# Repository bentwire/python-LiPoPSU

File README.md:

# python-LiPoPSU
Python drivers and sundry for my LiPo PSU design in eagle

Boards can be ordered from OSH Park

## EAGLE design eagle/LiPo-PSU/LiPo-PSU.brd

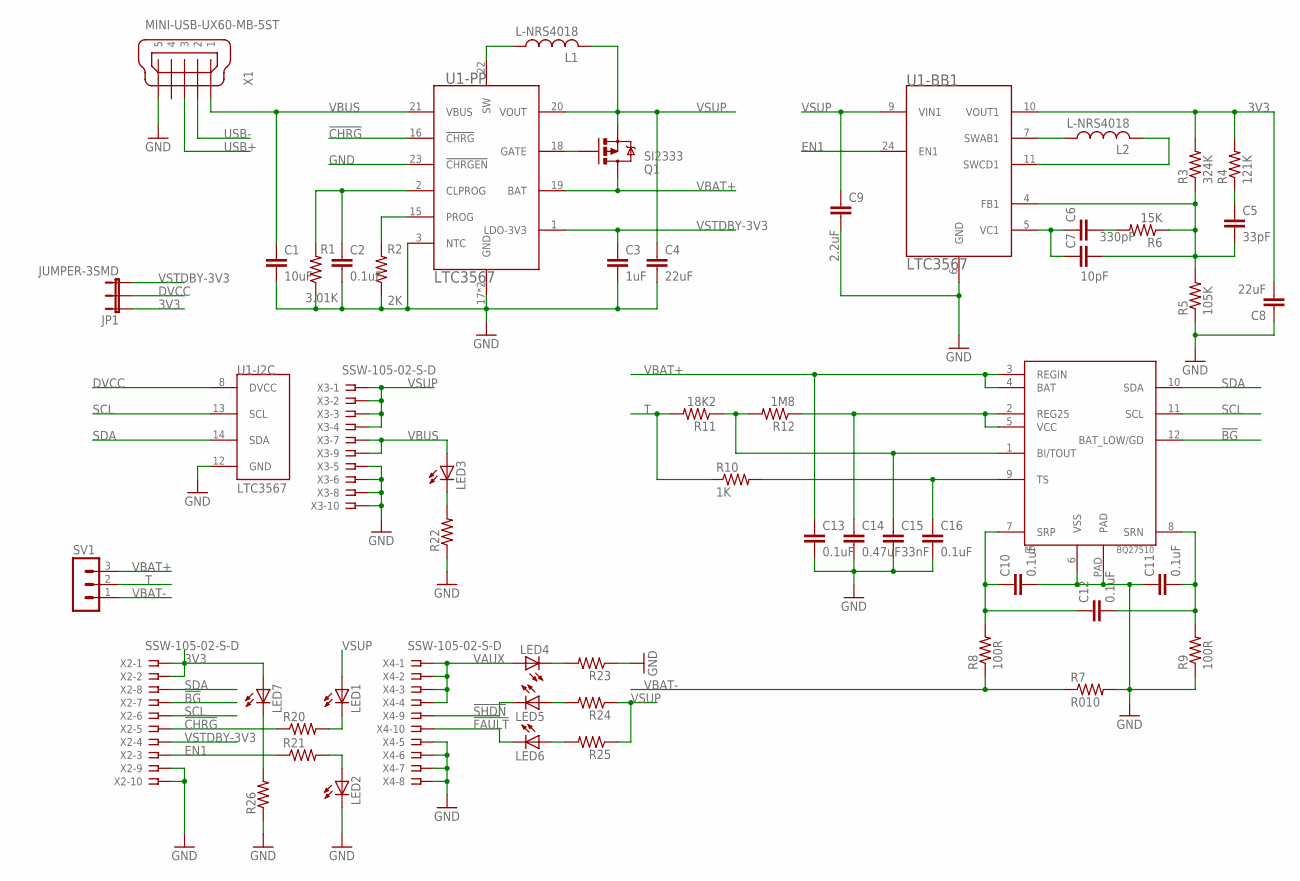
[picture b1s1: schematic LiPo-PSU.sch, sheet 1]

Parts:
C1: 10uF; 0805
C2: 0.1uF; 0402-CAP
C3: 1uF; 0402-CAP
C4, C8: 22uF; 0805
C5: 33pF; 0402-CAP
C6: 330pF; 0402-CAP
C7: 10pF; 0402-CAP
C9: 2.2uF; 0402-CAP
C10, C11, C12, C13, C16: 0.1uF; C0402
C14: 0.47uF; C0402
C15: 33nF; C0402
JP1: JUMPER-3SMD; SJ_3
L1, L2: L-NRS4018; NR(S)401X
LED1, LED2, LED3, LED4, LED5, LED6, LED7: LEDCHIP-LED0603; CHIP-LED0603
Q1: SI2333; SOT23-3
R1: 3.01K; 0402-RES
R2: 2K; 0402-RES
R3: 324K; 0402-RES
R4: 121K; 0402-RES
R5: 105K; 0402-RES
R6: 15K; 0402-RES
R7: R010; R2512
R8, R9: 100R; R0402
R10: 1K; R0402
R11: 18K2; R0402
R12: 1M8; R0402
R20, R21, R22, R23, R24, R25, R26: R-US_R0402; R0402
SV1: MA03-1
U1: LTC3567; QFN24-4X4(UF)
U3: BQ27510; DRZ(S-PDSO-N12)
X1: MINI-USB-UX60-MB-5ST; UX60-MB-5ST
X2, X3, X4: SSW-105-02-S-D

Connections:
3V3: C8.2, JP1.1, LED7.A, R3.2, R4.2, U1.10 (VOUT1), X2.1, X2.2; also elsewhere on the board
!BG: U3.12 (BAT_LOW/GD), X2.7
!CHRG!: R20.1, U1.16 (!CHRG!), X2.5
!FAULT: LED6.C, X4.10; also elsewhere on the board
!SHDN: LED5.C, X4.9; also elsewhere on the board
DVCC: JP1.2, U1.8 (DVCC)
EN1: R21.1, U1.24 (EN1), X2.3
GND: C1.2, C2.2, C3.2, C4.2, C8.1, C9.2, C10.2, C11.1, C13.2, C14.2, C15.2, C16.2, LED2.C, R1.1, R2.1, R5.1, R7.2, R9.1, R22.1, R23.1, R26.1, U1.3 (NTC), U1.6 (GND), U1.12 (GND), U1.17 (GND), U1.23 (!CHRGEN!), U1.PAD (GND), U3.6 (VSS), U3.PAD, X1.5, X2.9, X2.10, X3.5, X3.6, X3.8, X3.10, X4.5, X4.6, X4.7, X4.8; also elsewhere on the board
unnamed: L1.1, U1.22 (SW)
unnamed: C5.2, C7.2, R3.1, R5.2, R6.1, U1.4 (FB1)
unnamed: Q1.1 (G), U1.18 (GATE)
unnamed: L2.1, U1.7 (SWAB1)
unnamed: L2.2, U1.11 (SWCD1)
unnamed: C5.1, R4.1
unnamed: C15.1, R11.1, R12.2, U3.1 (BI/TOUT)
unnamed: C6.2, R6.2
unnamed: C6.1, C7.1, U1.5 (VC1)
unnamed: C2.1, R1.2, U1.2 (CLPROG)
unnamed: R2.2, U1.15 (PROG)
unnamed: LED1.C, R20.2
unnamed: C14.1, R12.1, U3.2 (REG25), U3.5 (VCC)
unnamed: LED2.A, R21.2
unnamed: LED3.C, R22.2
unnamed: LED5.A, R24.2
unnamed: LED6.A, R25.2
unnamed: LED4.C, R23.2
unnamed: LED7.C, R26.2
SCL: U1.13 (SCL), U3.11 (SCL), X2.6
SDA: U1.14 (SDA), U3.10 (SDA), X2.8
SRN: C11.2, C12.2, R9.2, U3.8 (SRN)
SRP: C10.1, C12.1, R8.2, U3.7 (SRP)
T: R10.1, R11.2, SV1.2
TIN: C16.1, R10.2, U3.9 (TS)
USB+: X1.3
USB-: X1.2
VAUX: LED4.A, X4.1, X4.2, X4.3, X4.4; also elsewhere on the board
VBAT+: C13.1, Q1.3 (D), SV1.3, U1.19 (BAT), U3.3 (REGIN), U3.4 (BAT)
VBAT-: R7.1, R8.1, SV1.1
VBUS: C1.1, LED3.A, U1.21 (VBUS), X1.1, X3.7, X3.9
VSTDBY-3V3: C3.1, JP1.3, U1.1 (LDO-3V3), X2.4
VSUP: C4.1, C9.1, L1.2, LED1.A, Q1.2 (S), R24.1, R25.1, U1.9 (VIN1), U1.20 (VOUT), X3.1, X3.2, X3.3, X3.4; also elsewhere on the board

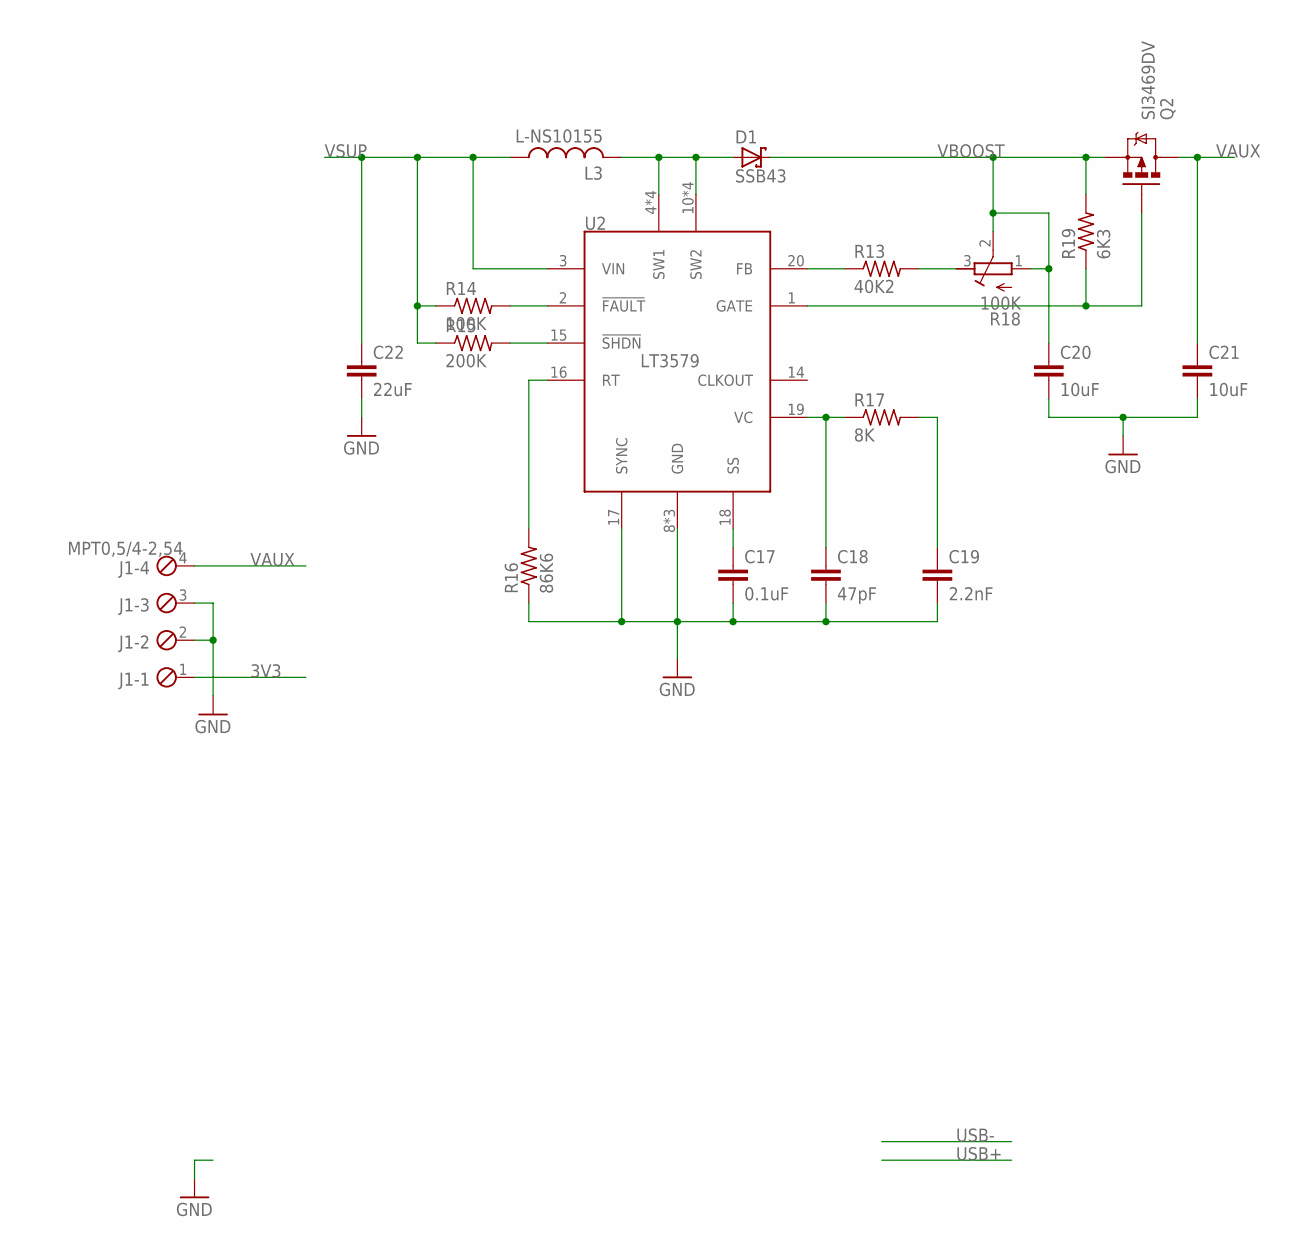
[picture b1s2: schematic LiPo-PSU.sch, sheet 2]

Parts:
C17: 0.1uF; C0402
C18: 47pF; C0402
C19: 2.2nF; C0402
C20, C21: 10uF; C0805
C22: 22uF; C0805
D1: SSB43; SMB
J1: MPT0,5/4-2,54
L3: L-NS10155; NS10155
Q2: SI3469DV; TSOP-6
R13: 40K2; R0402
R14: 100K; R0402
R15: 200K; R0402
R16: 86K6; R0402
R17: 8K; R0402
R18: 100K; RTRIM3214W
R19: 6K3; R0402
U2: LT3579; QFN20-4X5(UFD)

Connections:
3V3: J1.1; also elsewhere on the board
!FAULT: R14.2, U2.2 (!FAULT!); also elsewhere on the board
!SHDN: R15.2, U2.15 (!SHDN!); also elsewhere on the board
BOOST-FB: R13.1, U2.20 (FB)
GATE: Q2.3 (G), R19.1, U2.1 (GATE)
GND: C17.2, C18.2, C19.2, C20.2, C21.2, C22.2, J1.2, J1.3, R16.1, U2.8 (GND), U2.9 (GND), U2.17 (SYNC), U2.PAD (GND); also elsewhere on the board
unnamed: D1.A, L3.2, U2.4 (SW1), U2.5 (SW1), U2.6 (SW1), U2.7 (SW1), U2.10 (SW2), U2.11 (SW2), U2.12 (SW2), U2.13 (SW2)
unnamed: R13.2, R18.3 (A)
unnamed: R16.2, U2.16 (RT)
unnamed: C18.1, R17.1, U2.19 (VC)
unnamed: C19.1, R17.2
unnamed: C17.1, U2.18 (SS)
VAUX: C21.1, J1.4, Q2.1 (D), Q2.2 (D), Q2.5 (D), Q2.6 (D); also elsewhere on the board
VBOOST: C20.1, D1.C, Q2.4 (S), R18.1 (E), R18.2 (S), R19.2
VSUP: C22.1, L3.1, R14.1, R15.1, U2.3 (VIN); also elsewhere on the board

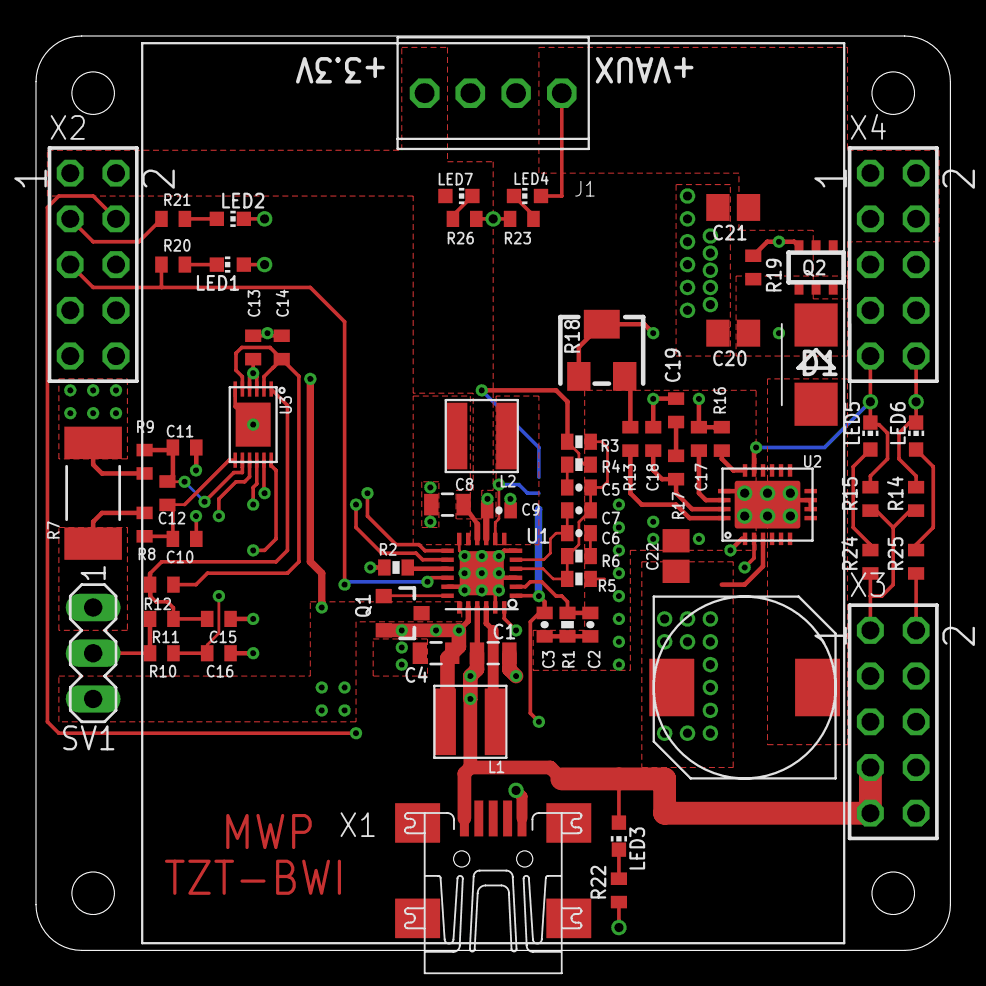
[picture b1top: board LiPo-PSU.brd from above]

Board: 4 copper layers, 50.8 x 50.8 mm, 72 parts (1 on the bottom side), 48 nets.

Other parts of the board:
U$1: LP503950

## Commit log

2016-03-08 Link to boards.
2016-03-08 Fix link.
2016-03-08 Started code.
2016-03-15 Added eagle CAD files.
2016-03-21 Flesh out the main functionality.
2016-03-29 Added command line utility.
2016-03-29 Add command line opts.
2016-03-29 Removed debug print.
2016-04-03 Added some more measurements (pt 1)
2016-04-03 Added some more measurements (pt 2)
2016-04-06 Retry on exception posting to influxdb
2016-04-09 Add temperature.
2016-04-09 Add TLS support...
2016-04-21 Implement simple logging
    Also, removing gpio stuff since it does not belong here.

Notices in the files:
parts and their libraries:
SparkFun: Licensing: CC v3.0 Share-Alike You are welcome to use this library for commercial purposes.
